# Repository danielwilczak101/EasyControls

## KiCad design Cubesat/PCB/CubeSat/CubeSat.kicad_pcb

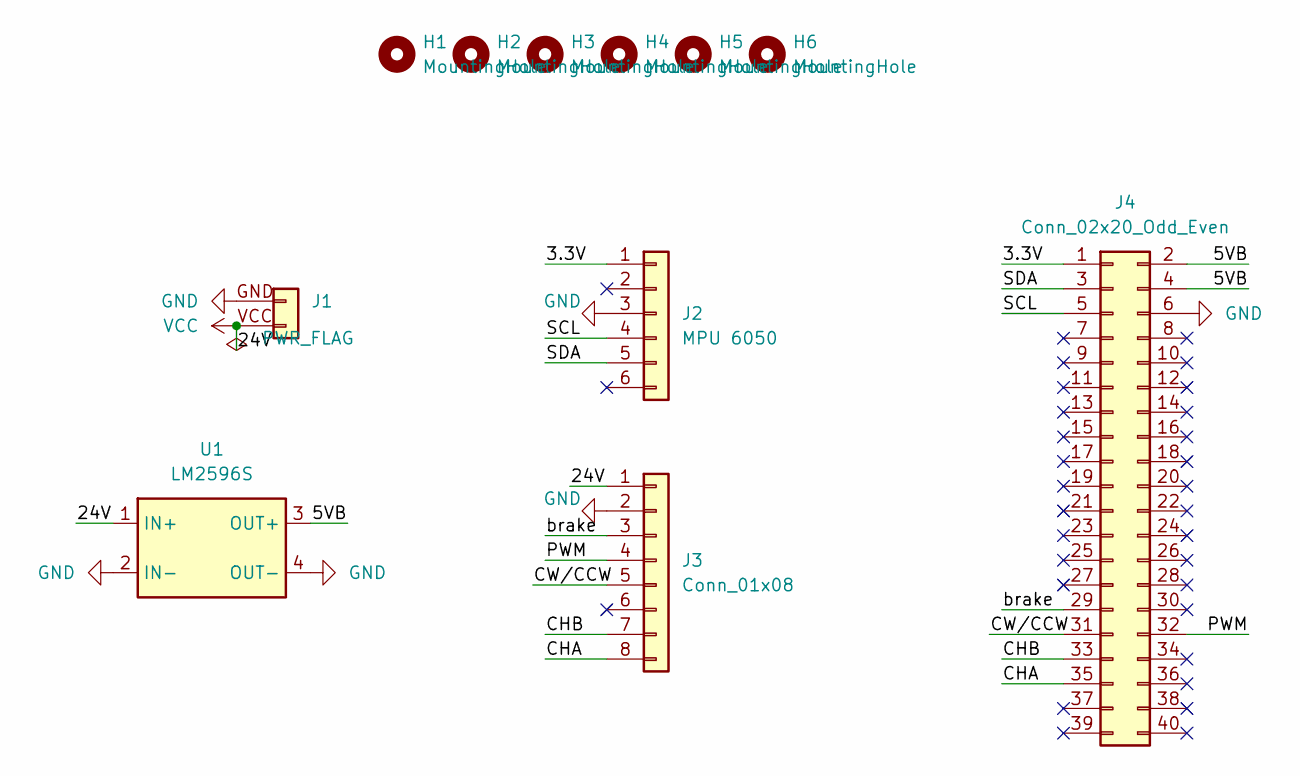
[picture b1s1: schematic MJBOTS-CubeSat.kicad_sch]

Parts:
H1, H2, H3, H4, H5, H6: MountingHole; MountingHole_2.5mm
J1: Li 24V Battery; 24V_Li_batt
J2: MPU 6050; PinHeader_1x06_P2.54mm_Vertical
J3: Conn_01x08; PinHeader_1x08_P2.54mm_Vertical
J4: Conn_02x20_Odd_Even; PinHeader_2x20_P2.54mm_Vertical
U1: LM2596S; LM2596S_mod

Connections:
/3.3V: J2.1, J4.1
/5VB: J4.2, J4.4, U1.3 (OUT+)
/CHA: J3.8, J4.35
/CHB: J3.7, J4.33
/CW/CCW: J3.5, J4.31
/PWM: J3.4, J4.32
/SCL: J2.4, J4.5
/SDA: J2.5, J4.3
/brake: J3.3, J4.29
GND: J1.GND (Pin_1), J2.3, J3.2, J4.6, U1.2 (IN-), U1.4 (OUT-)
VCC: J1.VCC (Pin_2), J3.1, U1.1 (IN+)

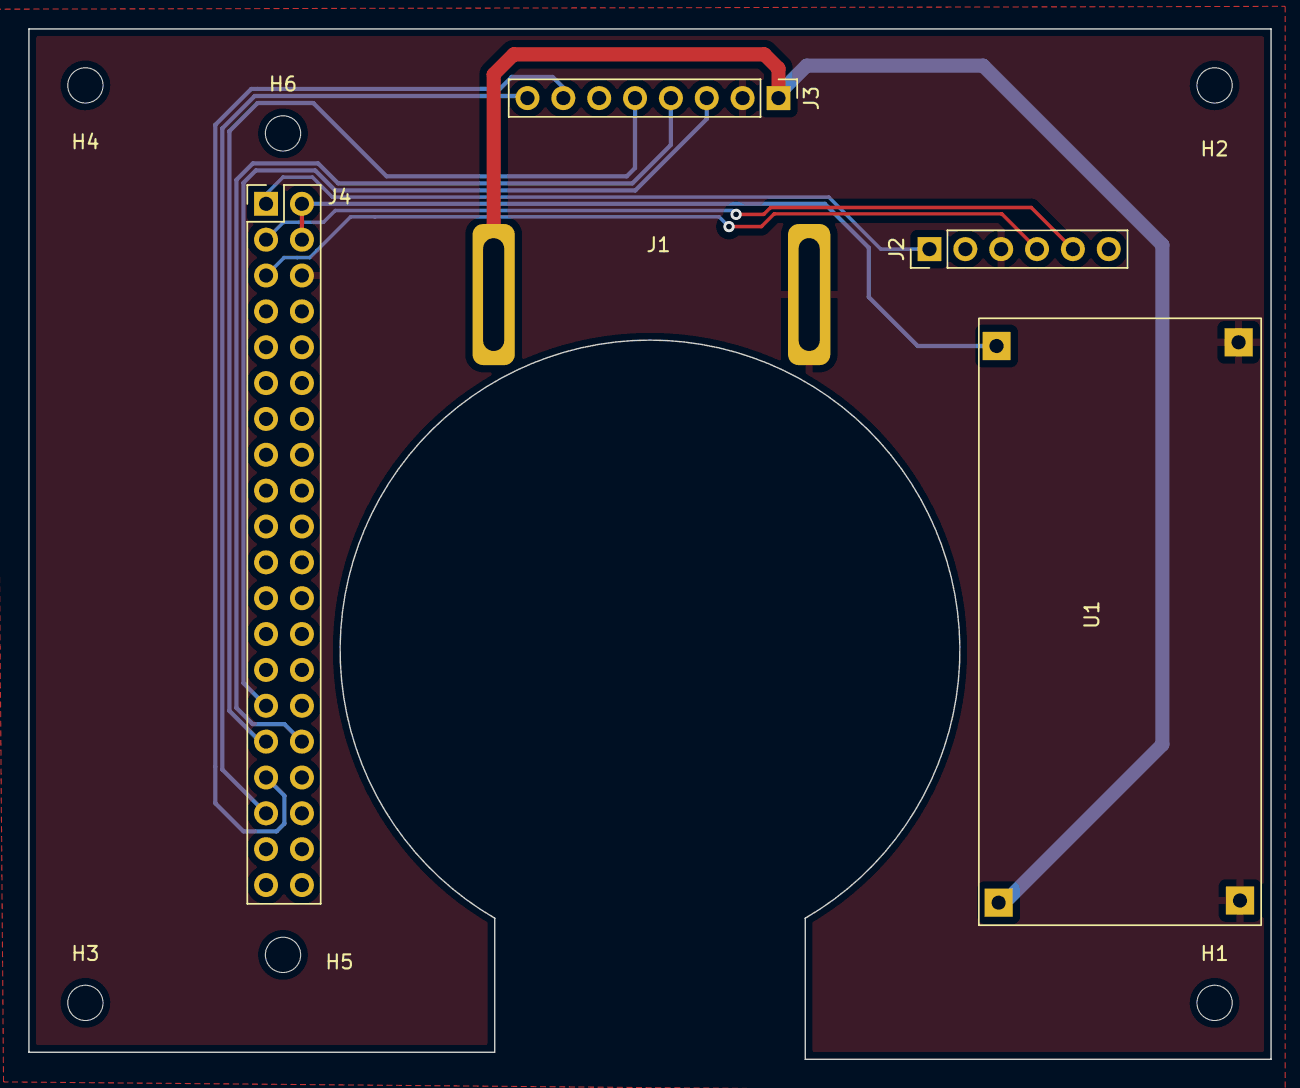
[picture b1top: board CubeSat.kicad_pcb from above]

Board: 2 copper layers, 88.0 x 73.0 mm, 11 parts (0 on the bottom side), 11 nets.

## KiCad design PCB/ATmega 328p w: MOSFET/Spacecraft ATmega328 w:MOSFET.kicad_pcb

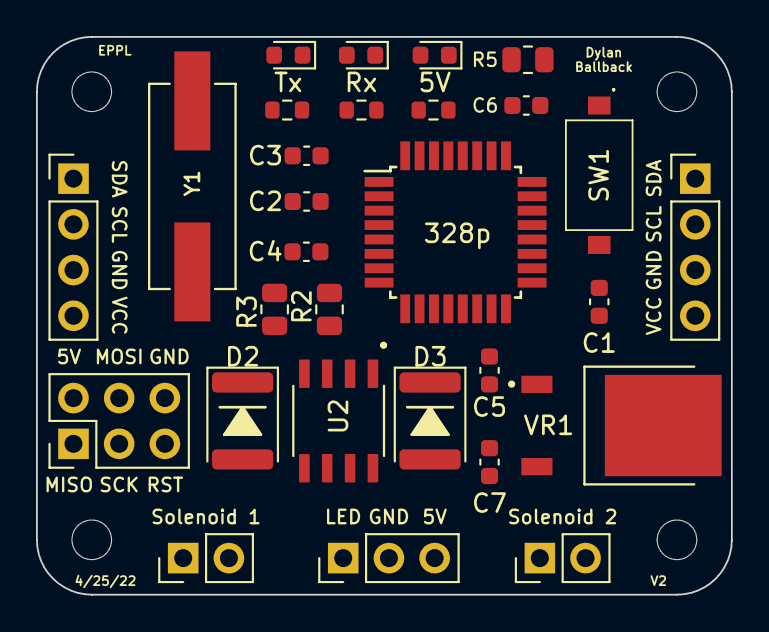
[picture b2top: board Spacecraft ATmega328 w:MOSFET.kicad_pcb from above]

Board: 2 copper layers, 38.6 x 31.0 mm, 33 parts (0 on the bottom side), 21 nets, no tracks yet.

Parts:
5V: LED; LED_0603_1608Metric
328p: ATmega328P-AU; TQFP-32_7x7mm_P0.8mm
C1, C2, C6: 100nF; C_0603_1608Metric
C3, C4: 22pf; C_0603_1608Metric
C5: 0.33 uF; C_0603_1608Metric
C7: 0.1uF; C_0603_1608Metric
D2, D3: D; D_1812_4532Metric
H1, H2, H3, H4: MountingHole; MountingHole_2.2mm_M2
J1, J2: I2C/Power_IN; PinHeader_1x04_P2.54mm_Vertical
J3: Bootloader Pins; PinHeader_2x03_P2.54mm_Vertical
J4: LED; PinHeader_1x03_P2.54mm_Vertical
J5: SOL_1; PinHeader_1x02_P2.54mm_Vertical
Jv: SOL_2; PinHeader_1x02_P2.54mm_Vertical
R2, R3, R5: 10k; R_0805_2012Metric
R6, R7, R8: 300; R_0603_1608Metric
Rx: LED; LED_0603_1608Metric
SW1: SW_Push; PTS636SK25SMTRLFS
Tx: LED; LED_0603_1608Metric
U2: DMN4026SSD; SOIC127P600X150-8N
VR1: LM78M05CDTX_NOPB; TO228P991X255-3N
Y1: Crystal; XTAL_ECS-160-20-5PXDN-TR

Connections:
+5V: 5V.2, 328p.4, 328p.6, 328p.18, C1.1, C2.1, C7.1, J3.2, J4.3, R5.1, VR1.3
/Gate1: 328p.10, R2.1, U2.2
/Gate2: 328p.11, R3.1, U2.4
/LED: 328p.9, J4.1
/MISO: 328p.16, J3.1
/MOSI: 328p.15, J3.4
/RXD: 328p.30, Rx.2
/Reset: 328p.29, C6.2, J3.5, R5.2, SW1.1
/SCK: 328p.17, J3.3
/SCL: 328p.28, J1.2, J2.2
/SDA: 328p.27, J1.1, J2.1
/SOL1: D2.2, J5.2, U2.5, U2.6
/SOL2: D3.2, Jv.2, U2.7, U2.8
/TXD: 328p.31, Tx.2
GND: 328p.3, 328p.5, 328p.21, C1.2, C2.2, C3.1, C4.1, C5.2, C6.1, C7.2, J1.3, J2.3, J3.6, J4.2, R2.2, R3.2, R6.1, R7.1, R8.1, SW1.2, U2.1, U2.3, VR1.4
unnamed: 328p.7, C3.2, Y1.1
unnamed: 328p.8, C4.2, Y1.2
unnamed: 5V.1, R6.2
unnamed: R7.2, Tx.1
unnamed: R8.2, Rx.1
VCC: C5.1, D2.1, D3.1, J1.4, J2.4, J5.1, Jv.1, VR1.1

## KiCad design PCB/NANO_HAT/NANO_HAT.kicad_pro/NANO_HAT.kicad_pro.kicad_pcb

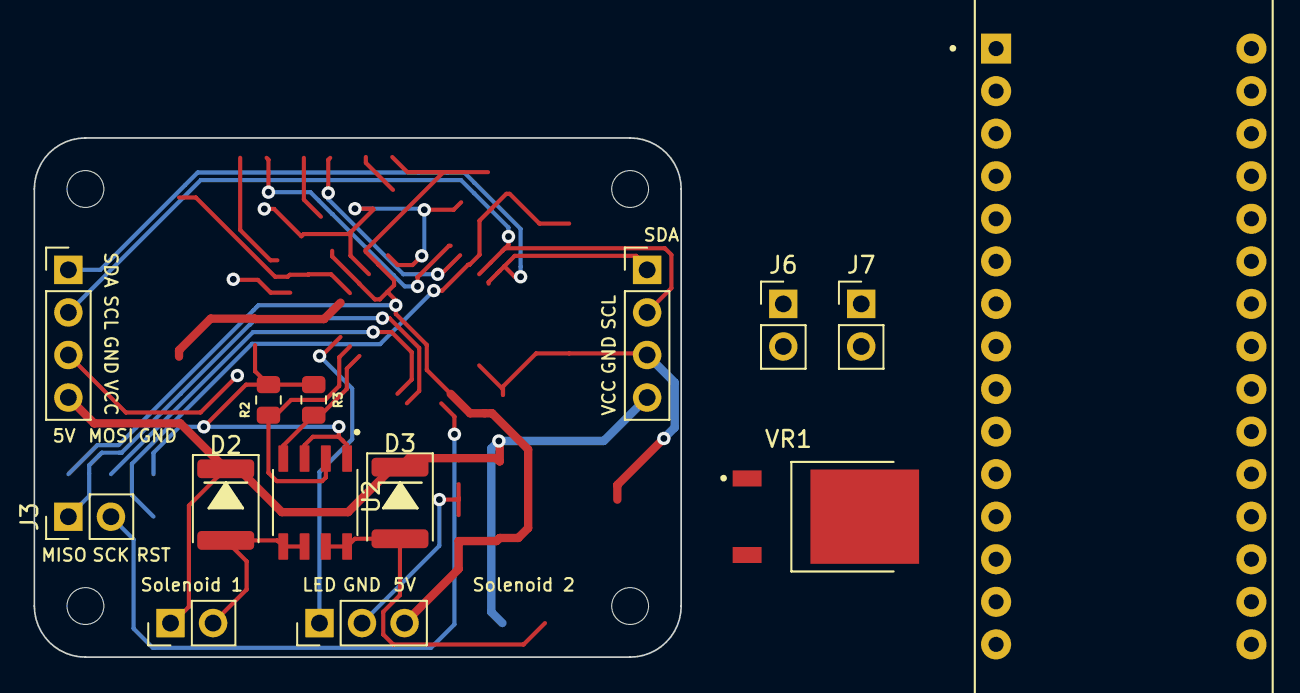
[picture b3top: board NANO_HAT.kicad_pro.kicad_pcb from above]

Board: 2 copper layers, 38.6 x 31.0 mm, 18 parts (0 on the bottom side), 10 nets.

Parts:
D2, D3: D; D_1812_4532Metric
H1, H2, H3, H4: MountingHole; MountingHole_2.2mm_M2
J1, J2: I2C/Power_IN; PinHeader_1x04_P2.54mm_Vertical
J3, J5: SOL_1; PinHeader_1x02_P2.54mm_Vertical
J4: LED; PinHeader_1x03_P2.54mm_Vertical
J6, J7: SOL_2; PinHeader_1x02_P2.54mm_Vertical
R2, R3: 10k; R_0805_2012Metric
TB1: ARDUINO_NANO; SHIELD_ARDUINO_NANO
U2: DMN4026SSD; SOIC127P600X150-8N
VR1: LM78M05CDTX/NOPB; TO228P991X255-3N

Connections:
/5V: TB1.30 (VIN), VR1.3 (OUTPUT)
/Gate1: R2.1, U2.2 (G1)
/Gate2: R3.1, U2.4 (G2)
/LED: J4.2, TB1.8 (D5)
/SCL: J1.2, J2.2, TB1.24 (A5)
/SDA: J1.1, J2.1, TB1.23 (A4)
/SOL1: D2.2 (A), J3.2, J5.2, TB1.9 (D6), U2.5 (D1), U2.6 (D1)
/SOL2: D3.2 (A), J6.2, J7.2, TB1.10 (D7), U2.7 (D2), U2.8 (D2)
GND: J1.3, J2.3, J4.3, R2.2, R3.2, TB1.4 (COM/GND), TB1.29 (COM/GND), U2.1 (S1), U2.3 (S2), VR1.4 (GND)
VCC: D2.1 (K), D3.1 (K), J1.4, J2.4, J3.1, J5.1, J6.1, J7.1, VR1.1 (INPUT)

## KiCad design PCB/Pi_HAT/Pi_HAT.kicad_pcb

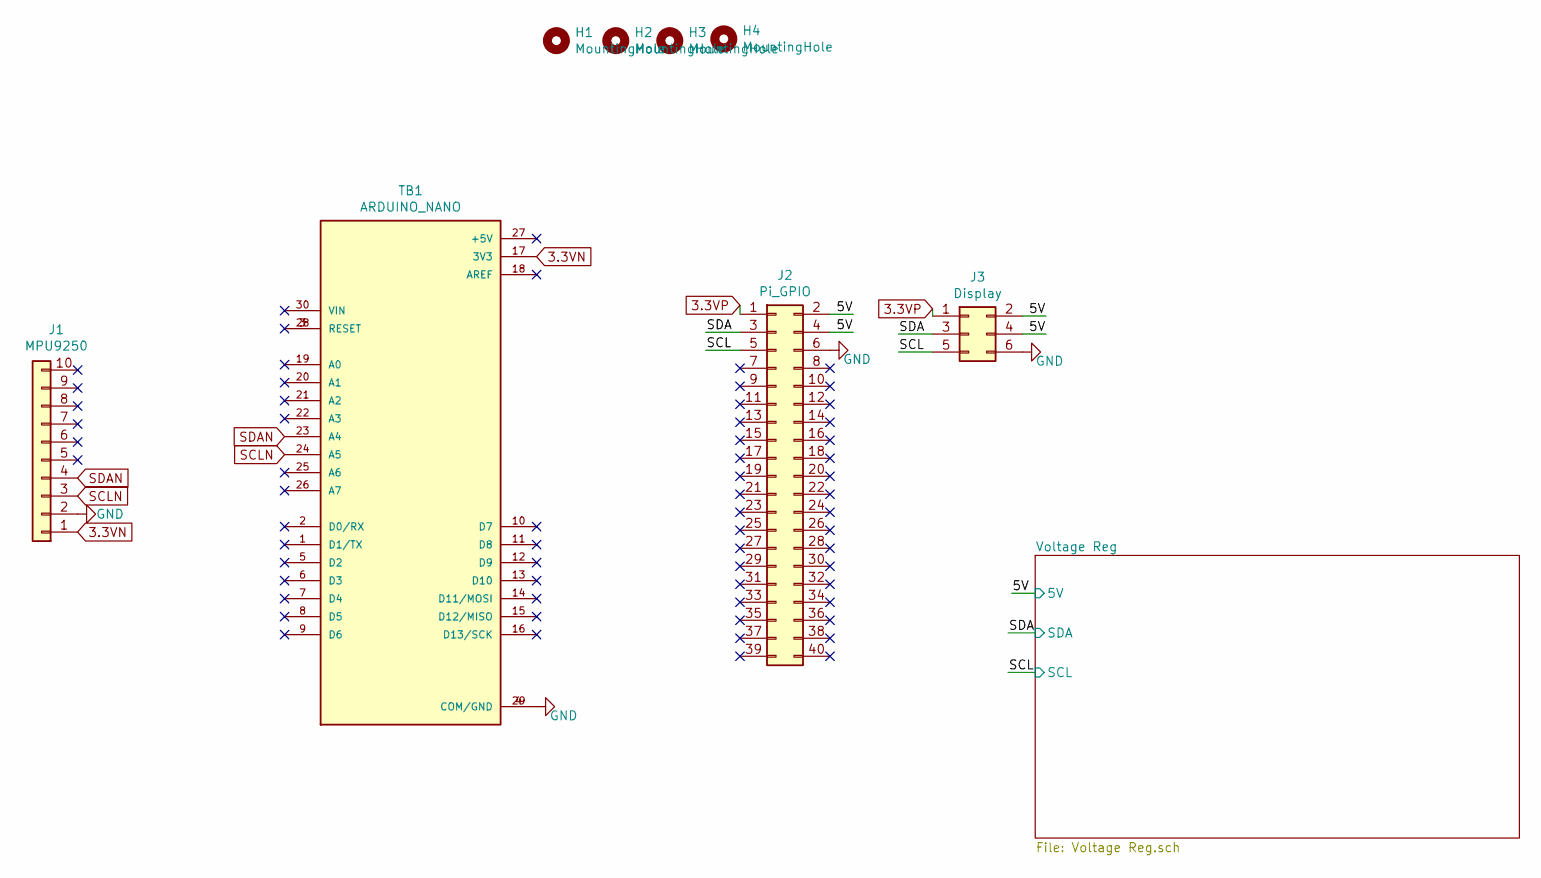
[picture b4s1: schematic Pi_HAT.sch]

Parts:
H1, H2, H3, H4: MountingHole; MountingHole_2.5mm
J1: MPU9250; PinHeader_1x10_P2.54mm_Vertical
J2: Pi_GPIO; PinHeader_2x20_P2.54mm_Vertical
J3: Display; PinHeader_2x03_P2.54mm_Vertical
TB1: ARDUINO_NANO; SHIELD_ARDUINO_NANO

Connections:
3.3VN: J1.1, TB1.17 (3V3)
3.3VP: J2.1, J3.1
/5V: J2.2, J2.4, J3.2, J3.4; also elsewhere on the board
/SCL: J2.5, J3.5; also elsewhere on the board
/SDA: J2.3, J3.3; also elsewhere on the board
GND: J1.2, J2.6, J3.6, TB1.4 (COM/GND), TB1.29 (COM/GND); also elsewhere on the board
unnamed: TB1.3 (RESET), TB1.28 (RESET)
SCLN: J1.3, TB1.24 (A5)
SDAN: J1.4, TB1.23 (A4)

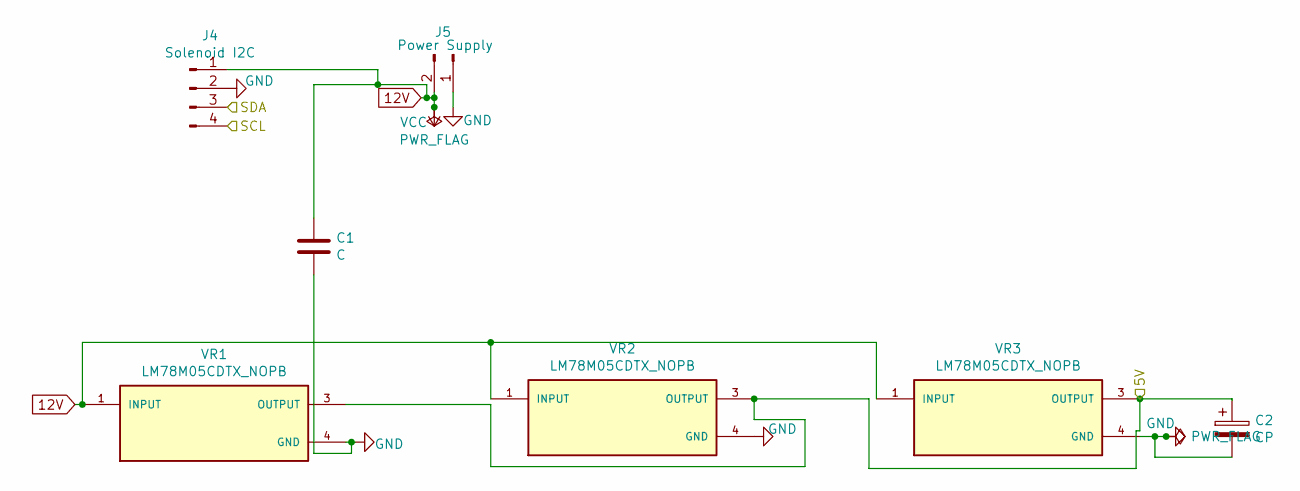
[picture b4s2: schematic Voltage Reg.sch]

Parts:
C1: C; C_Rect_L7.0mm_W2.5mm_P5.00mm
C2: CP; CP_Radial_D4.0mm_P1.50mm
J4: Solenoid I2C; PinHeader_1x04_P2.54mm_Vertical
J5: Power Supply; TerminalBlock_RND_205-00276_1x02_P5.00mm_Vertical
VR1, VR2, VR3: LM78M05CDTX_NOPB; TO228P991X255-3N; PARTREV G

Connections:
12V: C1.1, J4.1, J5.2, VR1.1 (INPUT), VR2.1 (INPUT), VR3.1 (INPUT)
/5V: C2.1, VR1.3 (OUTPUT), VR2.3 (OUTPUT), VR3.3 (OUTPUT); also elsewhere on the board
/SCL: J4.4; also elsewhere on the board
/SDA: J4.3; also elsewhere on the board
GND: C1.2, C2.2, J4.2, J5.1, VR1.4 (GND), VR2.4 (GND), VR3.4 (GND); also elsewhere on the board

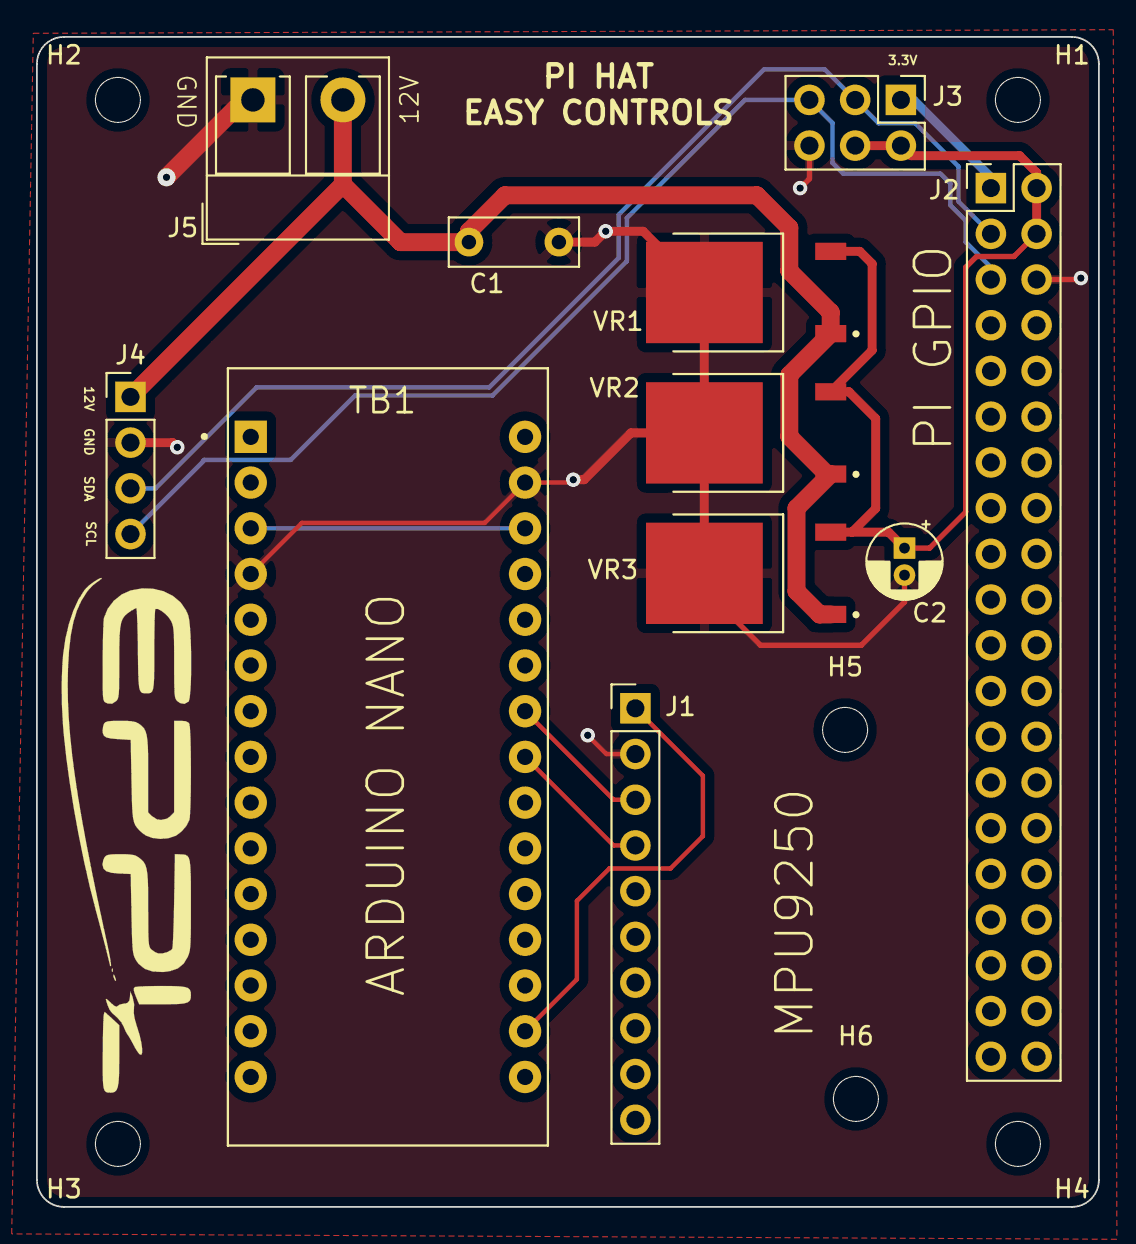
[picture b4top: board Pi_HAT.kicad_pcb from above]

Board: 2 copper layers, 59.0 x 65.0 mm, 17 parts (0 on the bottom side), 10 nets.

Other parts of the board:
H5, H6: MountingHole; MountingHole_2.5mm
